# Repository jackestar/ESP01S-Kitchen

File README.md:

<div align="center">
<h3>ESP01S controlled for a Resistive Element (Kitchen)</h3>

</div>

---

## Goal

Controlling a resistive AC heating element using an SSR (Solid State Relay) controlled by a ESP01S (ESP8266 based board)

* Push-button On/Off :heavy_check_mark:
* App Control (On/Off, Timer, Dimmer) :heavy_check_mark:
* OTA Update :heavy_check_mark:
* Translations :x:
* CI/CD (Github Actions) :x:

## Build

```
node build.mjs

cd Arduino

arduino-cli compile --fqbn esp8266:esp8266:generic:eesz=1M64 ESP01S-Kitchen

arduino-cli compile --fqbn esp8266:esp8266:generic:xtal=160,eesz=1M64 ESP01S-Kitchen

mklittlefs -c ESP01S-Kitchen/data -p 256 -b 4096 -s 0x10000 littlefs.bin

esptool.py --port /dev/ttyUSB0 write_flash 0xEB000 littlefs.bin
```

## Board and Schematics

[Articulo del Esquemático](https://jackestar.netlify.app/Blog/Kicad/ESP01S-Kitchen-Driver.html)

[Kicad Project](Kicad)

# License

**This Repo** - MIT License

**ESP8266 RTOS SDK** - Apache 2.0

**Material Symbols / Material Icons** - Apache 2.0

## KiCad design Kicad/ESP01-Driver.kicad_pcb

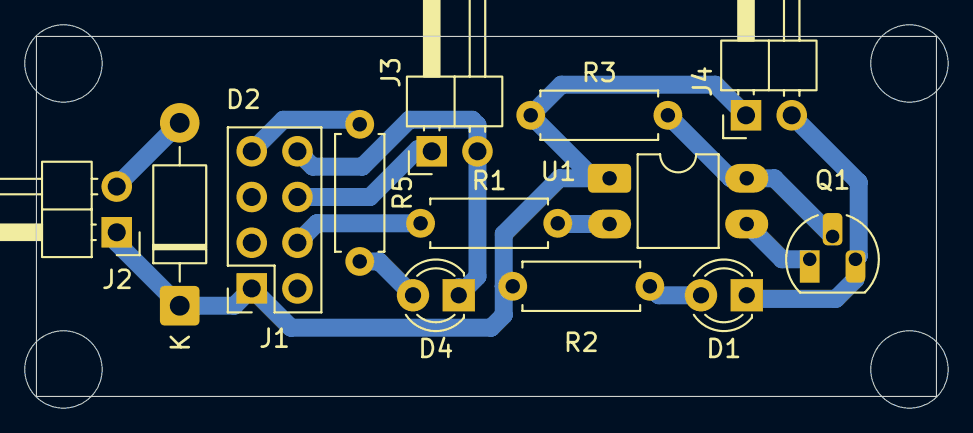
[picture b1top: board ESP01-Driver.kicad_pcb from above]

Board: 2 copper layers, 50.0 x 20.0 mm, 13 parts (0 on the bottom side), 10 nets.

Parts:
D1, D4: LED; LED_D3.0mm
D2: 3v6; D_DO-41_SOD81_P10.16mm_Horizontal
J1: ESP01S; PinSocket_2x04_P2.54mm_Vertical
J2: Supply; PinHeader_1x02_P2.54mm_Horizontal
J3: Push Button; PinHeader_1x02_P2.54mm_Horizontal
J4: Relay; PinHeader_1x02_P2.54mm_Horizontal
Q1: 2N2222A; TO-92_HandSolder
R1: 100; R_Axial_DIN0207_L6.3mm_D2.5mm_P7.62mm_Horizontal
R2, R5: 220; R_Axial_DIN0207_L6.3mm_D2.5mm_P7.62mm_Horizontal
R3: 3.3k; R_Axial_DIN0207_L6.3mm_D2.5mm_P7.62mm_Horizontal
U1: PC123; DIP-4_W7.62mm_LongPads

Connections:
+3V3: D2.1 (K), J1.1, J2.1, J4.1, R2.1, R3.1, U1.1
GND: D2.2 (A), D4.1 (K), J1.8, J2.2, J3.2, Q1.1 (E), U1.3
IO0: J1.4, R1.1
IO1/TX: J1.7, R5.1
IO2: J1.6, J3.1
unnamed: D1.2 (A), R2.2
unnamed: D1.1 (K), J4.2, Q1.3 (C)
unnamed: D4.2 (A), R5.2
unnamed: Q1.2 (B), R3.2, U1.4
unnamed: R1.2, U1.2

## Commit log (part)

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2025-08-10 Working Toggle H/S
2025-08-10 Clean
2025-08-12 Beta 1
2025-08-13 Beta 1 - Base Line (UI) Some sdkconfig pr mods
2025-08-13 Beta 2 (Release Candidate) New UI
2025-08-25 Beta 2 get state
2025-08-26 Update UI/UX Add +-10 min Button Upd each 1s fix Upd Readme Add Licence Upd sdkconfig (nothing to do)
2025-08-26 Upd Github Action
2025-08-26 skdconfig with UART (for no pathed version)
2025-08-27 Add Kicad Board Schematics Upd Preview Add Build Readme Upd Github action CI
2025-08-27 Github Action Test
2025-08-27 Another Github Action Test
2025-08-27 Fix Tag problem from Github Action
2025-08-27 One Last TIme Github Action Fix
2025-08-28 CI from own github action Update Readme
2025-08-28 Make and dont size it
